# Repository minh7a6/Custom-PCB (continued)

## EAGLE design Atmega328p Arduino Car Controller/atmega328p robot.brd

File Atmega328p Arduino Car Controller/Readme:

Remember to put a heatsink at the LM350 since it can get very hot during function

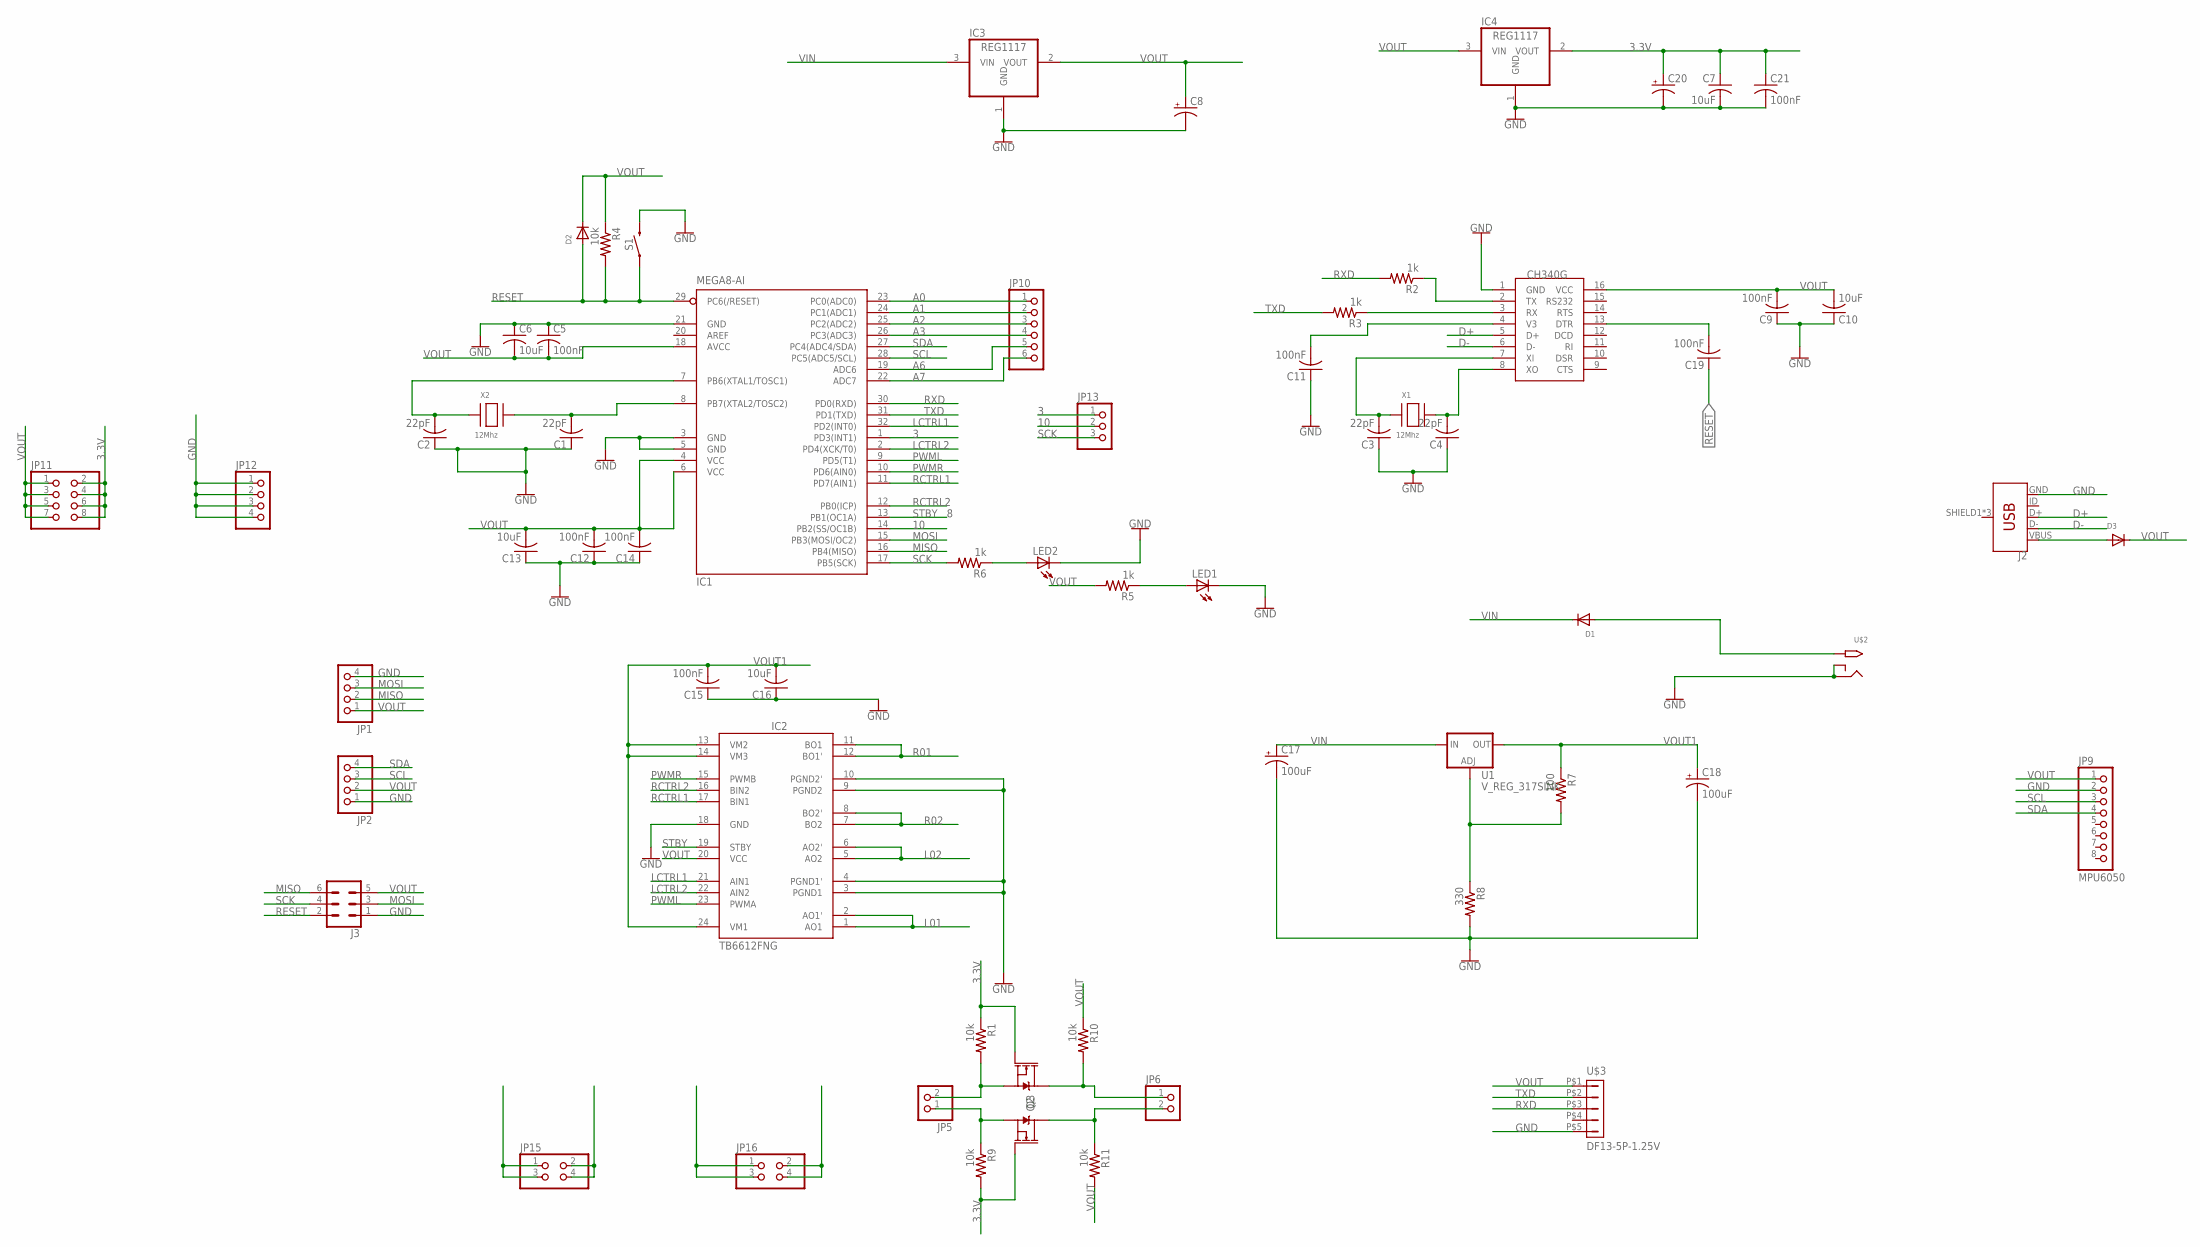
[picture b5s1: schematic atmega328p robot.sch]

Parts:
C1, C2, C3, C4: 22pF; C0805
C5, C9, C11, C12, C14, C15, C19, C21: 100nF; C0805
C6, C7, C10, C13, C16: 10uF; C0805
C8, C20: CPOL-USCT7343; CT7343
C17, C18: 100uF; CT7343
D1, D2, D3: DIODESOD-123; SOD-123
IC1: MEGA8-AI; TQFP32-08
IC2: TB6612FNG; SSOP24
IC3, IC4: REG1117; SOT223
J2: USB_MICRO-B_FEMALE-SMT; USB-B-MICRO-SMD
J3: CONN_03X22X3_SILK_MALE_PTH; 2X3
JP1, JP2, JP12: PINHD-1X4; 1X04
JP5, JP6: PINHD-1X2; 1X02
JP9: MPU6050; 1X08
JP10: PINHD-1X6; 1X06
JP11: PINHD-2X4; 2X04
JP13: PINHD-1X3; 1X03
JP15, JP16: PINHD-2X2; 2X02
LED1, LED2: LEDCHIP-LED0603; CHIP-LED0603
Q2, Q3: 220mA/50V/3.5Ω; SOT23-3
R1, R4, R9, R10, R11: 10k; R0805
R2, R3, R5, R6: 1k; R0805
R7: 100; R0805
R8: 330; R0805
S1: MOMENTARY-SWITCH-SPST-SMD-6.0X3.5MM; TACTILE_SWITCH_SMD_6.0X3.5MM
U1: V_REG_317SINK; TO220-ADJ
U$1: CH340G; SOIC16
U$2: 2.1MMJACKTHM; PJ-102A
U$3: DF13-5P-1.25V; DF13C-5P-1.25V
X1, X2: 12Mhz; NX5032

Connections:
3: IC1.1 (PD3(INT1)), JP13.1
3.3V: C7.1, C20.+, C21.1, IC4.2 (VOUT), JP11.2, JP11.4, JP11.6, JP11.8, Q2.1 (G), Q3.1 (G), R1.1, R9.2
10: IC1.14 (PB2(SS/OC1B)), JP13.2
A0: IC1.23 (PC0(ADC0)), JP10.1
A1: IC1.24 (PC1(ADC1)), JP10.2
A2: IC1.25 (PC2(ADC2)), JP10.3
A3: IC1.26 (PC3(ADC3)), JP10.4
A6: IC1.19 (ADC6), JP10.5
A7: IC1.22 (ADC7), JP10.6
D+: J2.D+, U$1.5 (D+)
D-: J2.D-, U$1.6 (D-)
GND: C1.1, C2.1, C3.1, C4.1, C5.1, C6.1, C7.2, C8.-, C9.1, C10.1, C11.1, C12.1, C13.1, C14.1, C15.1, C16.1, C17.-, C18.-, C20.-, C21.2, IC1.3 (GND), IC1.5 (GND), IC1.21 (GND), IC2.3 (PGND1), IC2.4 (PGND1'), IC2.9 (PGND2), IC2.10 (PGND2'), IC2.18 (GND), IC3.1 (GND), IC4.1 (GND), J2.GND, J3.1, JP1.4, JP2.1, JP9.2, JP12.1, JP12.2, JP12.3, JP12.4, LED1.C, LED2.C, R8.2, S1.2, U$1.1 (GND), U$2.RING, U$2.RING_SW, U$3.P$5 (5)
L01: IC2.1 (AO1), IC2.2 (AO1'), JP16.1, JP16.3
L02: IC2.5 (AO2), IC2.6 (AO2'), JP16.2, JP16.4
LCTRL1: IC1.32 (PD2(INT0)), IC2.21 (AIN1)
LCTRL2: IC1.2 (PD4(XCK/T0)), IC2.22 (AIN2)
MISO: IC1.16 (PB4(MISO)), J3.6, JP1.2
MOSI: IC1.15 (PB3(MOSI/OC2)), J3.3, JP1.3
unnamed: C2.2, IC1.7 (PB6(XTAL1/TOSC1)), X2.P$1
unnamed: C1.2, IC1.8 (PB7(XTAL2/TOSC2)), X2.P$2
unnamed: C19.2, U$1.13 (DTR)
unnamed: R2.1, U$1.2 (TX)
unnamed: C3.2, U$1.7 (XI), X1.P$1
unnamed: C4.2, U$1.8 (XO), X1.P$2
unnamed: LED1.A, R5.1
unnamed: R3.1, U$1.3 (RX)
unnamed: C11.2, U$1.4 (V3)
unnamed: LED2.A, R6.1
unnamed: D1.A, U$2.TIP
unnamed: R7.2, R8.1, U1.ADJ
unnamed: D3.A, J2.VBUS
PWML: IC1.9 (PD5(T1)), IC2.23 (PWMA)
PWMR: IC1.10 (PD6(AIN0)), IC2.15 (PWMB)
R01: IC2.11 (BO1), IC2.12 (BO1'), JP15.1, JP15.3
R02: IC2.7 (BO2), IC2.8 (BO2'), JP15.2, JP15.4
RCTRL1: IC1.11 (PD7(AIN1)), IC2.17 (BIN1)
RCTRL2: IC1.12 (PB0(ICP)), IC2.16 (BIN2)
RESET: C19.1, D2.A, IC1.29 (PC6(/RESET)), J3.2, R4.2, S1.1
RXD: IC1.30 (PD0(RXD)), R2.2, U$3.P$3 (3)
SCK: IC1.17 (PB5(SCK)), J3.4, JP13.3, R6.2
SCL: IC1.28 (PC5(ADC5/SCL)), JP2.3, JP6.2, JP9.3, Q3.3 (D), R11.1
SCL3.3: JP5.1, Q3.2 (S), R9.1
SDA: IC1.27 (PC4(ADC4/SDA)), JP2.4, JP6.1, JP9.4, Q2.3 (D), R10.2
SDA3.3: JP5.2, Q2.2 (S), R1.2
STBY: IC1.13 (PB1(OC1A)), IC2.19 (STBY)
TXD: IC1.31 (PD1(TXD)), R3.2, U$3.P$2 (2)
VIN: C17.+, D1.C, IC3.3 (VIN), U1.IN
VOUT: C5.2, C6.2, C8.+, C9.2, C10.2, C12.2, C13.2, C14.2, D2.C, D3.C, IC1.4 (VCC), IC1.6 (VCC), IC1.18 (AVCC), IC2.20 (VCC), IC3.2 (VOUT), IC4.3 (VIN), J3.5, JP1.1, JP2.2, JP9.1, JP11.1, JP11.3, JP11.5, JP11.7, R4.1, R5.2, R10.1, R11.2, U$1.16 (VCC), U$3.P$1 (1)
VOUT1: C15.2, C16.2, C18.+, IC2.13 (VM2), IC2.14 (VM3), IC2.24 (VM1), R7.1, U1.OUT

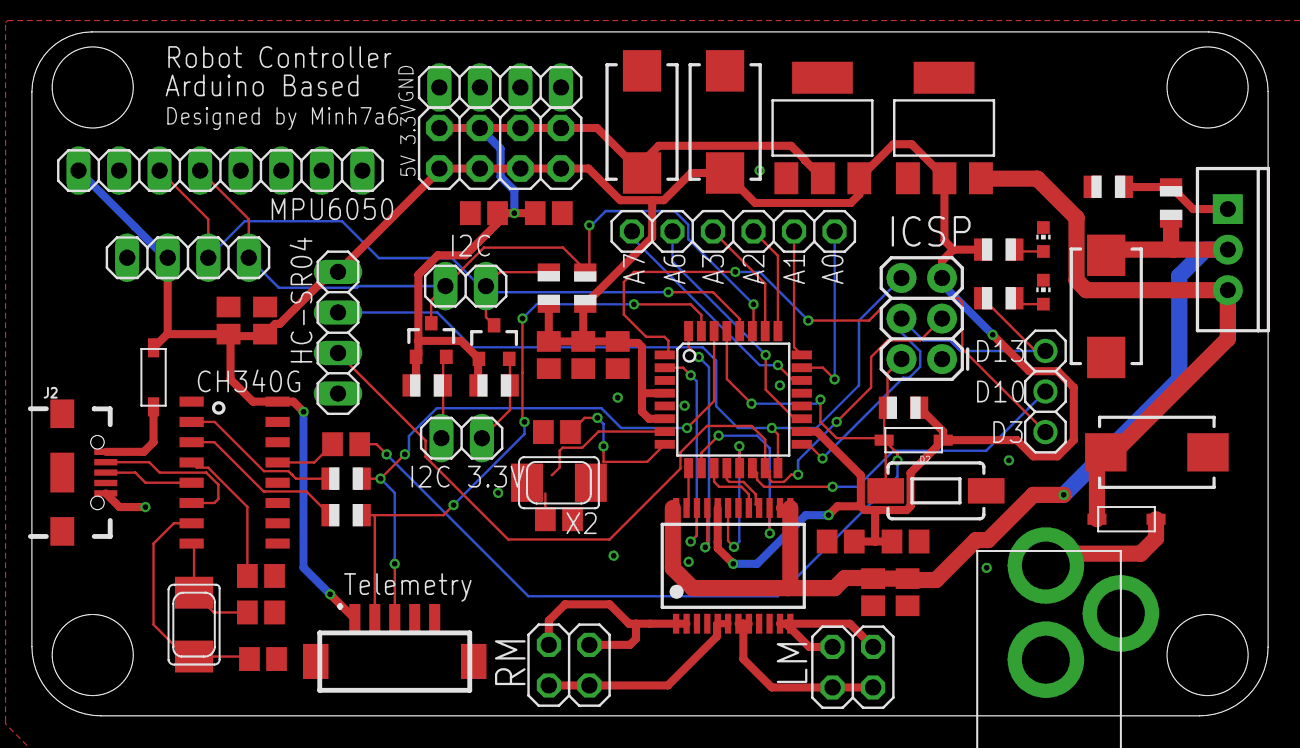
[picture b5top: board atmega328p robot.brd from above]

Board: 2 copper layers, 77.5 x 42.9 mm, 63 parts (0 on the bottom side), 49 nets.

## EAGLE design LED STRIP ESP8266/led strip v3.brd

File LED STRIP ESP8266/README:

PCB File for Custom ESP-12 LED STRIP

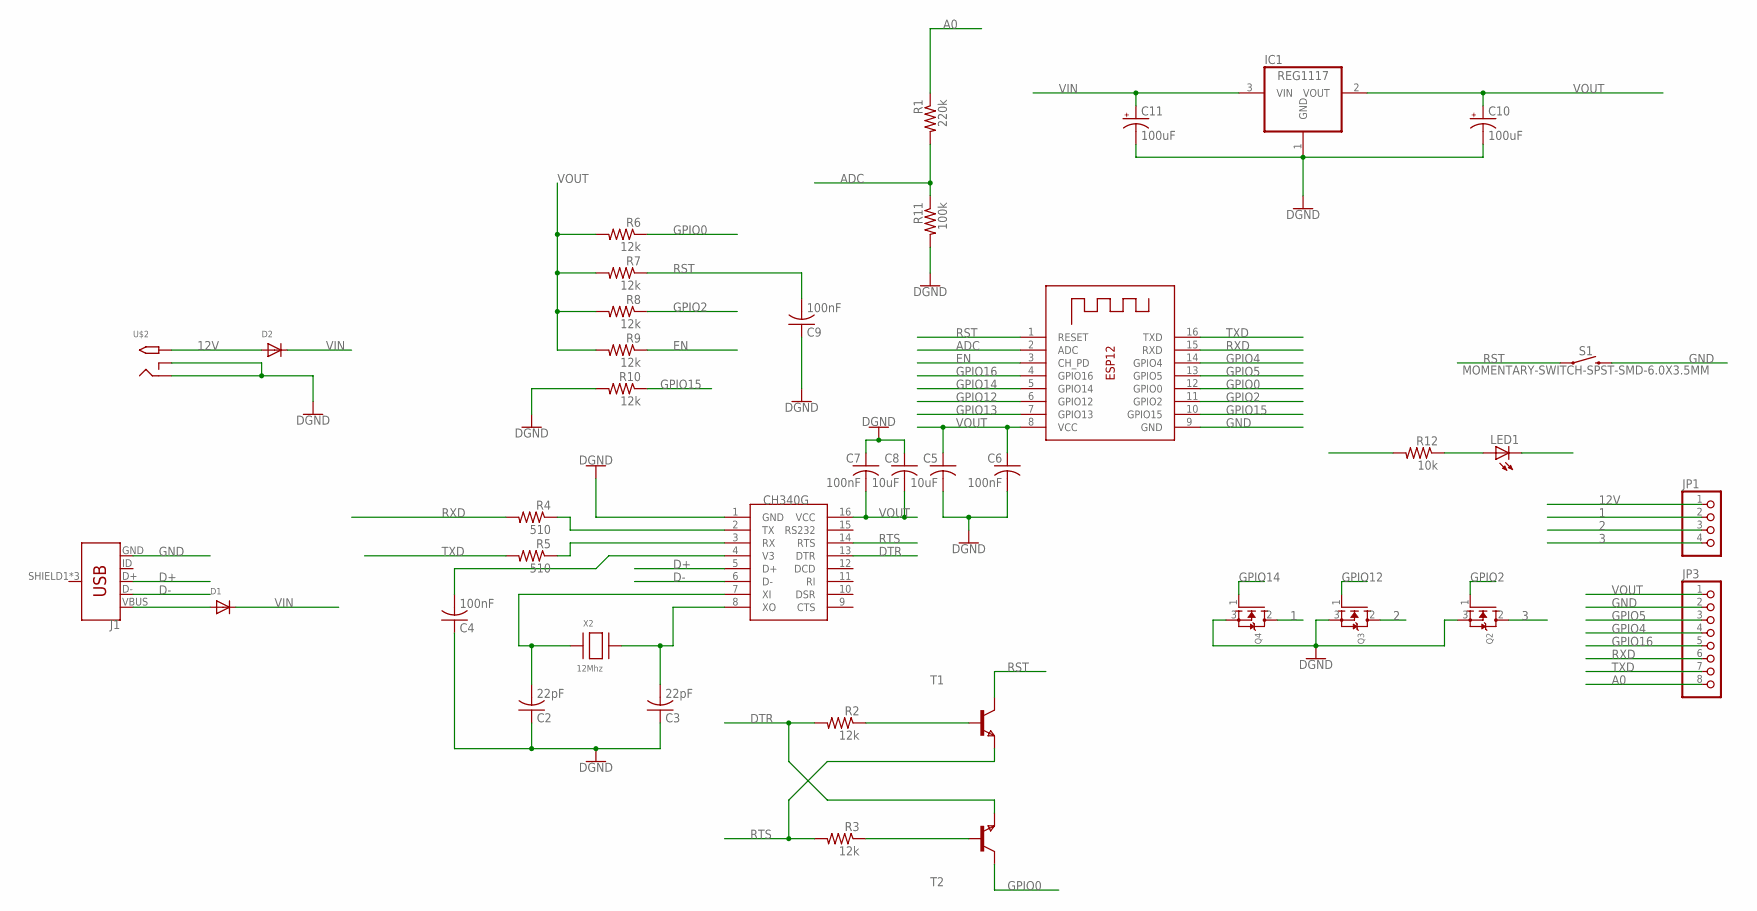
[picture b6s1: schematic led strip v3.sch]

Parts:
C2, C3: 22pF; C0805
C4, C6, C7, C9: 100nF; C0805
C5, C8: 10uF; C0805
C10, C11: 100uF; CT7343
D1, D2: DIODESOD-123; SOD-123
IC1: REG1117; SOT223
J1: USB_MICRO-B_FEMALE-SMT; USB-B-MICRO-SMD
JP1: PINHD-1X4; 1X04
JP3: PINHD-1X8; 1X08
LED1: LEDCHIP-LED0603; CHIP-LED0603
Q2, Q3, Q4: MOSFET-NGDS_TO220V; TO220V
R1: 220k; R0805
R2, R3, R6, R7, R8, R9, R10: 12k; R0805
R4, R5: 510; R0805
R11: 100k; R0805
R12: 10k; R0805
S1: MOMENTARY-SWITCH-SPST-SMD-6.0X3.5MM; TACTILE_SWITCH_SMD_6.0X3.5MM
T1, T2: NPNSOT23; SOT-23
U$1: CH340G; SOIC16
U$2: 2.1MMJACKTHM; PJ-102A
X1: ESP-12
X2: 12Mhz; NX5032

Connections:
1: JP1.2, Q4.2 (D)
2: JP1.3, Q3.2 (D)
3: JP1.4, Q2.2 (D)
12V: D2.A, JP1.1, U$2.TIP
A0: JP3.8, R1.1
ADC: R1.2, R11.1, X1.2 (ADC)
D+: J1.D+, U$1.5 (D+)
D-: J1.D-, U$1.6 (D-)
DTR: R2.2, T2.2 (E), U$1.13 (DTR)
EN: R9.1, X1.3 (CH_PD)
GND: C2.1, C3.1, C4.1, C5.2, C6.2, C7.1, C8.1, C9.1, C10.-, C11.-, IC1.1 (GND), J1.GND, JP3.2, LED1.C, Q2.3 (S), Q3.3 (S), Q4.3 (S), R10.2, R11.2, S1.2, U$1.1 (GND), U$2.RING, U$2.RING_SW, X1.9 (GND)
GPIO0: R6.1, T2.1 (C), X1.12 (GPIO0)
GPIO2: Q2.1 (G), R8.1, X1.11 (GPIO2)
GPIO4: JP3.4, X1.14 (GPIO4)
GPIO5: JP3.3, X1.13 (GPIO5)
GPIO12: Q3.1 (G), X1.6 (GPIO12)
GPIO13: X1.7 (GPIO13)
GPIO14: Q4.1 (G), X1.5 (GPIO14)
GPIO15: R10.1, X1.10 (GPIO15)
GPIO16: JP3.5, X1.4 (GPIO16)
unnamed: R2.1, T1.3 (B)
unnamed: R3.1, T2.3 (B)
unnamed: D1.A, J1.VBUS
unnamed: LED1.A, R12.1
unnamed: C2.2, U$1.7 (XI), X2.P$1
unnamed: C3.2, U$1.8 (XO), X2.P$2
unnamed: R4.1, U$1.2 (TX)
unnamed: R5.1, U$1.3 (RX)
unnamed: C4.2, U$1.4 (V3)
RST: C9.2, R7.1, S1.1, T1.1 (C), X1.1 (RESET)
RTS: R3.2, T1.2 (E), U$1.14 (RTS)
RXD: JP3.6, R4.2, X1.15 (RXD)
TXD: JP3.7, R5.2, X1.16 (TXD)
VIN: C11.+, D1.C, D2.C, IC1.3 (VIN)
VOUT: C5.1, C6.1, C7.2, C8.2, C10.+, IC1.2 (VOUT), JP3.1, R6.2, R7.2, R8.2, R9.2, R12.2, U$1.16 (VCC), X1.8 (VCC)

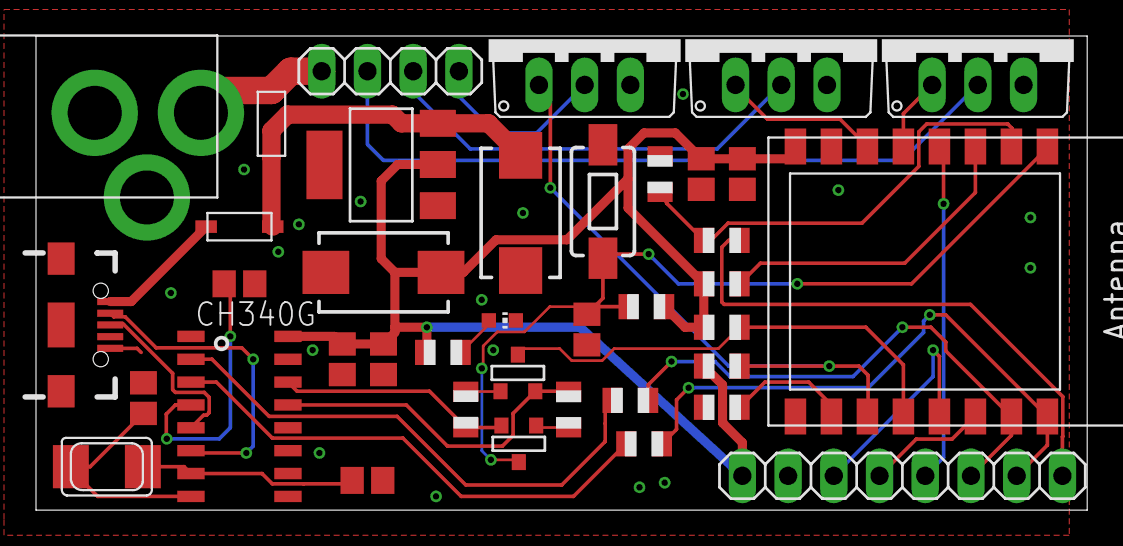
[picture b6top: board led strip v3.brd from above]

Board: 2 copper layers, 58.4 x 26.3 mm, 39 parts (0 on the bottom side), 34 nets.

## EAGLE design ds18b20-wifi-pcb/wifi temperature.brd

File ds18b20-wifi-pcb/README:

This is ds18b20 Temperature sensor custom board based on Wemos D1 Mini. For Arduino coding, choose Wemos D1 R2 & Mini as your board.
There is an error: GPIO4 and GPIO5 is in wrong position, they should be in the reverse way. Notice that when you code.
Enjoy :)

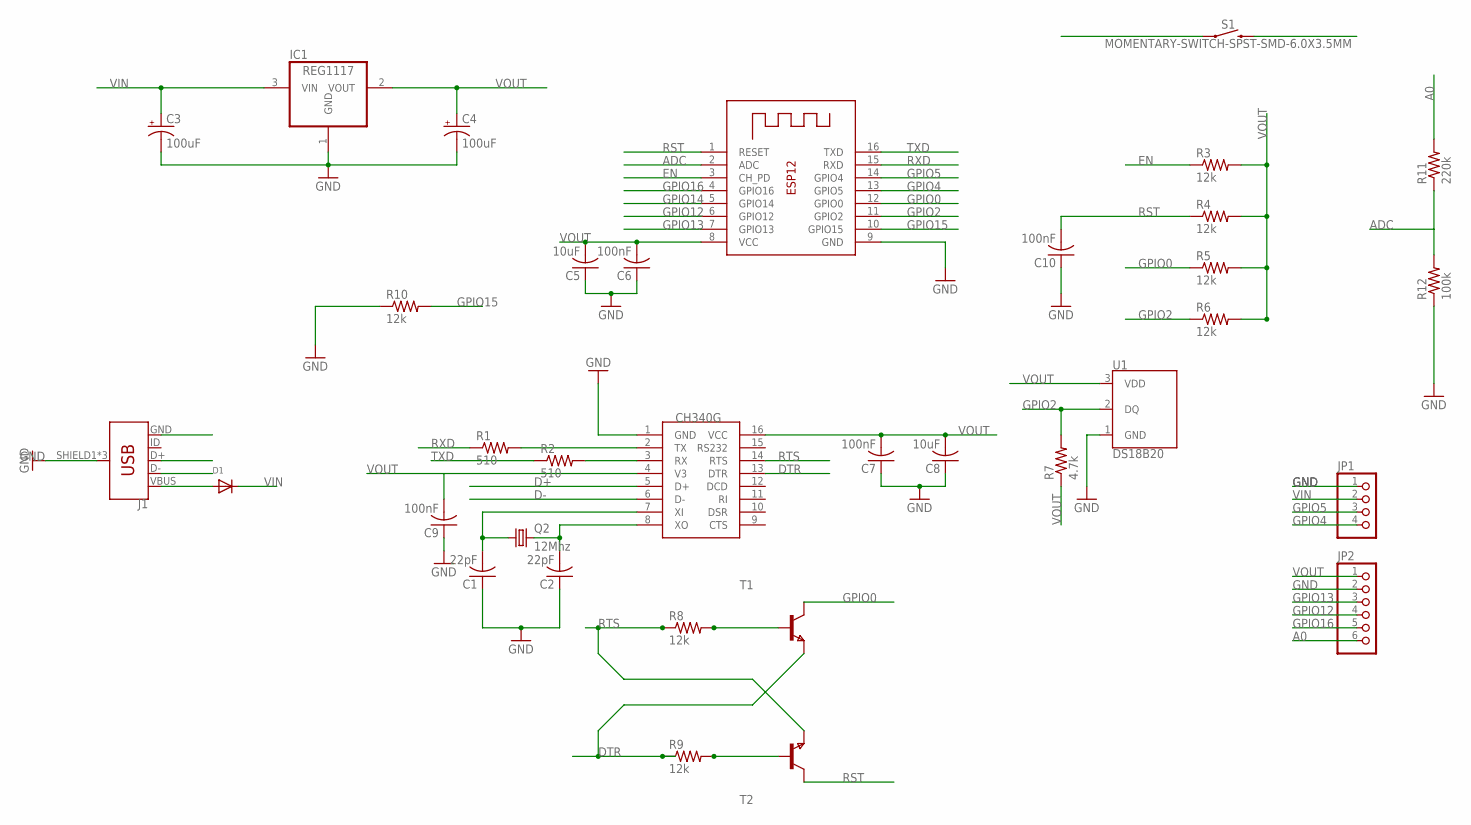
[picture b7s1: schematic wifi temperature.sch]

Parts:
C1, C2: 22pF; C0805
C3, C4: 100uF; CT7343
C5, C8: 10uF; C0805
C6, C7, C9, C10: 100nF; C0805
D1: DIODESOD-123; SOD-123
IC1: REG1117; SOT223
J1: USB_MICRO-BREDUCED_PASTE; USB-B-MICRO-SMD_RED_PASTE
JP1: PINHD-1X4; 1X04
JP2: PINHD-1X6; 1X06
Q2: 12Mhz; HC49/S
R1, R2: 510; R0805
R3, R4, R5, R6, R8, R9, R10: 12k; R0805
R7: 4.7k; R0805
R11: 220k; R0805
R12: 100k; R0805
S1: MOMENTARY-SWITCH-SPST-SMD-6.0X3.5MM; TACTILE_SWITCH_SMD_6.0X3.5MM
T1, T2: NPNSOT23; SOT-23
U1: DS18B20; TO-92-AMMO
U$1: CH340G; SOIC16
X1: ESP-12

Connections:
A0: JP2.6, R11.2
ADC: R11.1, R12.2, X1.2 (ADC)
D+: J1.D+, U$1.5 (D+)
D-: J1.D-, U$1.6 (D-)
DTR: R9.1, T1.2 (E), U$1.13 (DTR)
EN: R3.1, X1.3 (CH_PD)
GND: C1.1, C2.1, C3.-, C4.-, C5.1, C6.1, C7.1, C8.1, C9.1, C10.1, IC1.1 (GND), J1.GND, JP1.1, JP2.2, R10.1, R12.1, S1.2, U1.1 (GND), U$1.1 (GND), X1.9 (GND)
GPIO0: R5.1, T1.1 (C), X1.12 (GPIO0)
GPIO2: R6.1, R7.2, U1.2 (DQ), X1.11 (GPIO2)
GPIO4: JP1.4, X1.13 (GPIO5)
GPIO5: JP1.3, X1.14 (GPIO4)
GPIO12: JP2.4, X1.6 (GPIO12)
GPIO13: JP2.3, X1.7 (GPIO13)
GPIO14: X1.5 (GPIO14)
GPIO15: R10.2, X1.10 (GPIO15)
GPIO16: JP2.5, X1.4 (GPIO16)
unnamed: C1.2, Q2.1, U$1.7 (XI)
unnamed: C2.2, Q2.2, U$1.8 (XO)
unnamed: R8.2, T1.3 (B)
unnamed: R9.2, T2.3 (B)
unnamed: R1.2, U$1.2 (TX)
unnamed: R2.2, U$1.3 (RX)
unnamed: D1.A, J1.VBUS
RST: C10.2, R4.1, S1.1, T2.1 (C), X1.1 (RESET)
RTS: R8.1, T2.2 (E), U$1.14 (RTS)
RXD: R1.1, X1.15 (RXD)
TXD: R2.1, X1.16 (TXD)
VIN: C3.+, D1.C, IC1.3 (VIN), JP1.2
VOUT: C4.+, C5.2, C6.2, C7.2, C8.2, C9.2, IC1.2 (VOUT), JP2.1, R3.2, R4.2, R5.2, R6.2, R7.1, U1.3 (VDD), U$1.4 (V3), U$1.16 (VCC), X1.8 (VCC)

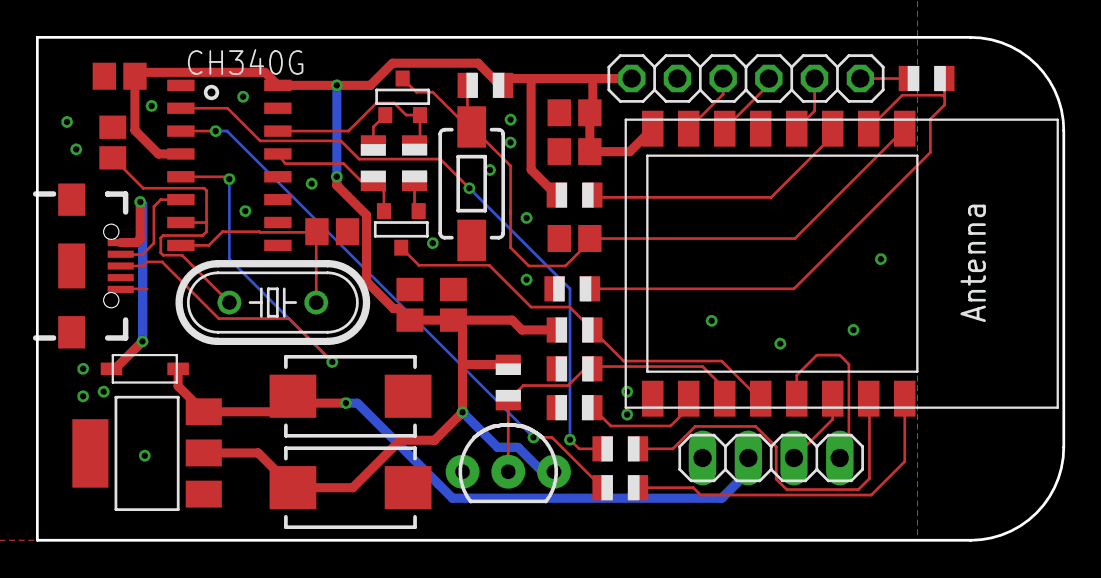
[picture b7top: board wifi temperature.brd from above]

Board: 2 copper layers, 57.0 x 27.9 mm, 34 parts (0 on the bottom side), 28 nets.

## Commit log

2017-12-14 Create wifi board
